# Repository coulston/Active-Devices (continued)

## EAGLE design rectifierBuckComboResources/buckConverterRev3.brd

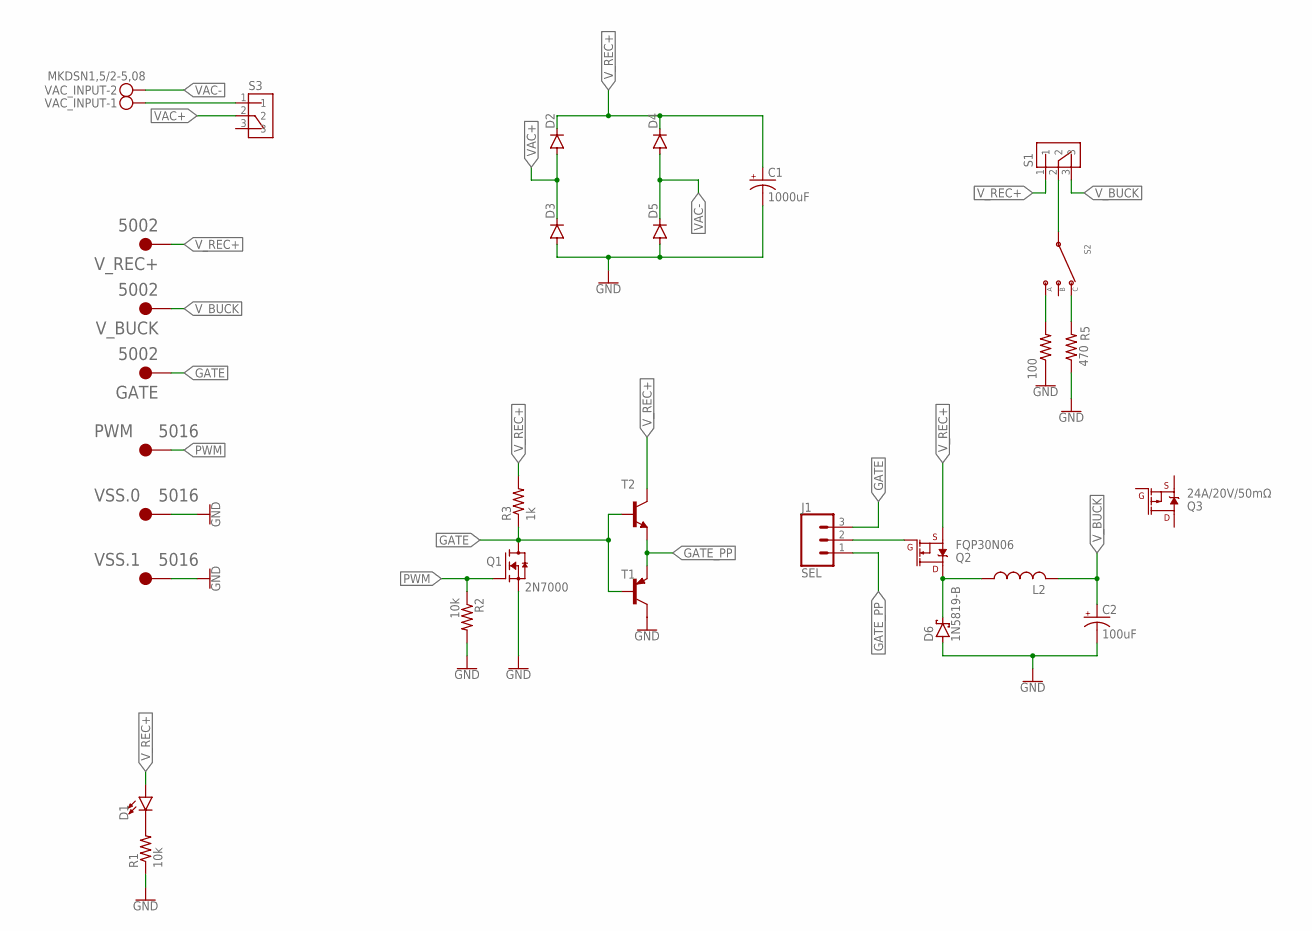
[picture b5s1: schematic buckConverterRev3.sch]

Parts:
C1: 1000uF; SANYO-OSCON_F13
C2: 100uF; SANYO-OSCON_C
D1: LED5MM; LED_5MM
D2, D3, D4, D5: DIODE-DO41-7.6; DO41-7.6
D6: 1N5819-B; DO41-7.6
GATE: 5002; KEYSTONE_5002
J1: SEL; 1X03_LOCK_LONGPADS
L2: L-US6000-XXX-RC; 6000-XXXX-RC
PWM: 5016; KEYSTONE_5016
Q1: 2N7000; TO92254P458H750-3
Q2: FQP30N06; TO220V
Q3: 24A/20V/50mΩ; TO220V
R1, R2: 10k; 0207/10
R3: 1k; 0207/10
R4: 100; 0617/22
R5: 470; 0309/12
S1: OS102011MS2QN1; SW_OS102011MS2QN1
S2: OS103011MS8QP1; OS102011MS8QP1
S3: ON/OFF; SW_OS102011MS2QN1
T1: 2N3906-PNP-TO92-EBC; TO92-EBC
T2: 2N3904-NPN-TO92-EBC; TO92-EBC
VAC_INPUT: MKDSN1,5/2-5,08
VSS.0, VSS.1: 5016; KEYSTONE_5016
V_BUCK: 5002; KEYSTONE_5002
V_REC+: 5002; KEYSTONE_5002

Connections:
100OHM: R4.2, S2.1
470OHM: R5.2, S2.4 (3)
GATE: GATE.TP, J1.3, Q1.3 (D), R3.1, T1.B, T2.B
GATE_PP: J1.1, T1.E, T2.E
GND: C1.-, C2.-, D3.A, D5.A, D6.A, Q1.1 (S), R1.1, R2.2, R4.1, R5.1, T1.C, VSS.0.TP, VSS.1.TP
unnamed: S3.1, VAC_INPUT.1
unnamed: D1.K (C), R1.2
unnamed: S1.2, S2.2 (C)
unnamed: J1.2, Q2.1 (G)
PWM: PWM.TP, Q1.2 (G), R2.1
SOURCE: D6.C, L2.1, Q2.2 (D)
VAC+: D2.A, D3.C, S3.2
VAC-: D4.A, D5.C, VAC_INPUT.2
V_BUCK: C2.+, L2.2, S1.3, V_BUCK.TP
V_REC+: C1.+, D1.A, D2.C, D4.C, Q2.3 (S), R3.2, S1.1, T2.C, V_REC+.TP

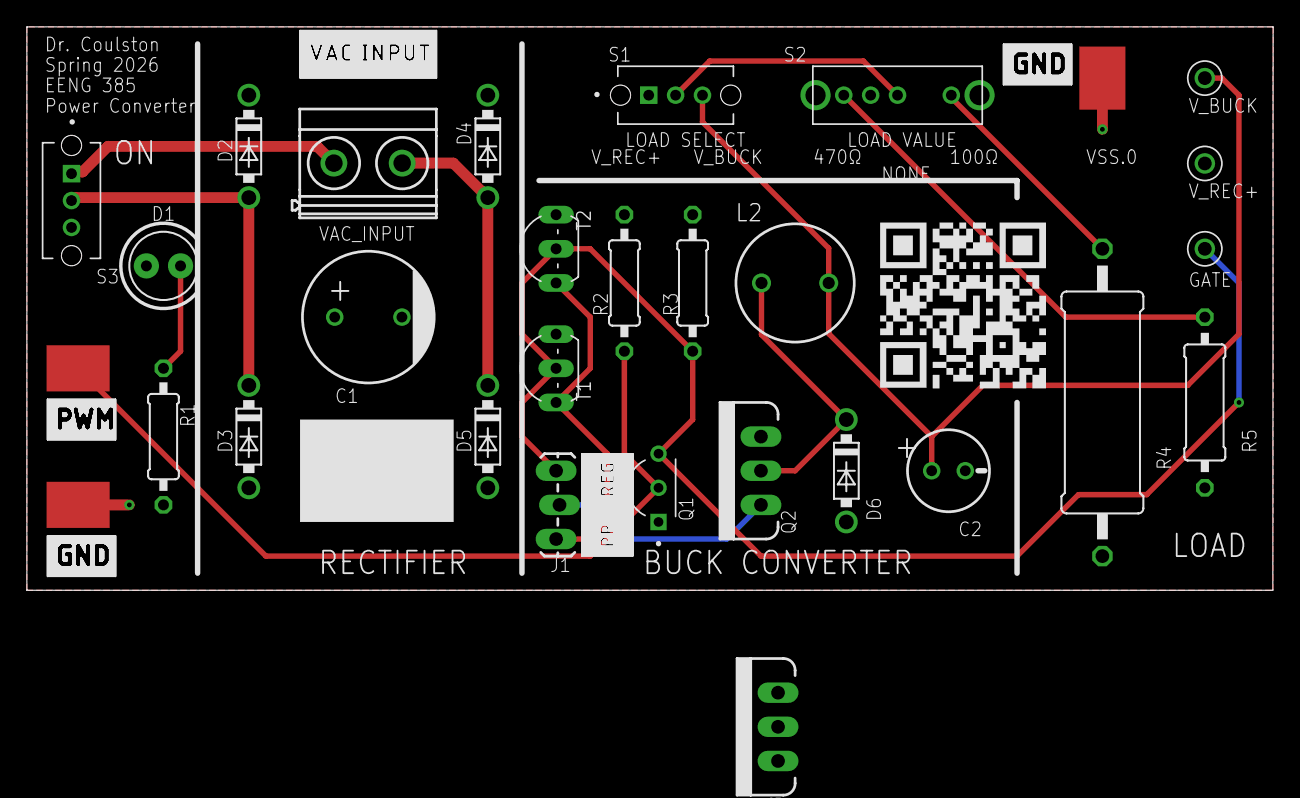
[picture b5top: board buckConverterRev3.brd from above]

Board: 2 copper layers, 92.7 x 41.9 mm, 30 parts (0 on the bottom side), 15 nets.

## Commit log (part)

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2024-11-20 Initial upload of lab documents
2024-12-02 Curve Tracer Labs
    Moved the assembly instructions out of first two labs so that they are less voluminous.
2024-12-03 Formatting and Assembly Guide
    Changed the Heading 1 and 2 formatting for every lab so that PDF will (hopefully) export them in an outline format. Also split off the assembly instructions into a separate document to reduce the pag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
2024-12-05 Added pcb materials
    Added EGLE CAD files as well as Gerber files for the PCBs and the bill of materials for both board - these need to be double checked.
2024-12-06 Clean up labs
2024-12-06 Added outcomes to first set of labs
    Making outcomes and objectives nomenclature consistent with the Digital Logic labs.
2024-12-12 added outcomes and objectives
2025-05-31 Update .gitignore
    Repository intended for students, so only show finished PDF document
2025-06-04 Move PCB files to top level
2025-09-25 Update .gitignore
    I am uploading the workbook and want to suppress the solutions and irrelevant files.
2025-09-25 Test push to check .gitignore
2025-09-25 workbook upload
    The big upload
2025-09-26 not sure??
2025-11-17 Adding PID Controller Lab
2025-11-18 Assembly instructions for PID controller PCB
2025-11-18 pid controller lab
2025-11-20 Lab exam uploads
    Basic Lab Exam information that is safe to share with students.
2025-12-16 Minor changes
2025-12-21 Pushing most recent changes
    To the PID controller lab
2025-12-23 Adding schematic
2025-12-28 updated lab
2025-12-30 workbook updates for spring 26
2026-01-02 Spring 2026 Workbook updates
    Made the master PDF
2026-01-19 Audio board modifications
    Added a bias resistor and emitter degeneration resistors to the audio board and had to edit an annoying amount of material.
2026-01-22 Adding Two PCBs
    Adding the Recifier with Buck and the PID Controller
2026-01-26 Create rectifierWithBuckDocument.pdf
    Getting the Power Supply PCBs and Lab write-up ready. Just need some pictures and to write up all the solutions
2026-01-26 Update rectifierWithBuckDocument.pdf
    Put some hard work to straighten out the solutions and wording.,
2026-01-29 Rectifier/Buck laboratory
    Finished the first iteration of the rectifier buck converter laboratory
2026-02-03 Complete PID Controller lab
    Put this lab to bed.
2026-02-12 Update final summary table
    Removed misleading information from one of the tables.
2026-02-19 Fix grammar/ambiguous sentences
2026-02-19 grammar fix and ambiguous sentence fix
2026-02-26 grammar and sentence fixes
2026-02-26 Typo: 2N7000 is NMOS not NPN
2026-03-05 Grammar fix
2026-03-05 typo fix use the ~~current~~ **voltage** from the previous problem to help you find the [current thru the rstistor]
2026-03-05 ignore lock files
2026-03-13 grammar fixes
2026-03-30 Create README.md
    An introduction to the material contained.
2026-03-30 Add CC logos
    I want others to use these materials and adapt them for their use. The CC license lets them know they can do this with confidence.
2026-05-05 Create readme.md
    Provide a landing page for anyone interested in the PID controller.
2026-05-05 Update license.md
    fixed image links
2026-05-05 Update the file name
2026-05-05 Add manufacturing files
2026-05-05 Video Timeline
2026-05-30 Ltspice Simulation
    The conversion from MultiSim Live to LTSpice means that I needed to re-write all the simulations. They all are done.
2026-06-12 some LTspice
2026-06-12 branch confusion???
2026-06-12 continued update for LTspice
2026-06-24 LTspice Instructions
2026-06-26 More LTspice
